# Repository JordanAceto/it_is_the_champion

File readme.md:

# 15 Watt Single Ended Tube Guitar Amp

- ## GU50 Pentode output
- ## Trainwreck style preamp
- ## It is the champion

---

## [SCHEMATIC](https://github.com/JordanAceto/it_is_the_champion/blob/main/pcb/docs/it_is_the_champion-schematic.pdf)

---
A prototype has been constructed and evaluated using a 6550 output tube. See the [prototype write up](https://github.com/JordanAceto/it_is_the_champion/blob/main/prototype/it_is_the_champion_prototype_write_up.pdf) for details. It sounds pretty good to me.

The GU50 output stage has been breadboarded. It seems to work well and gives a smidge more power out than the 6550 (I'm mostly just using it to be a hipster though).

Next steps:

Task | Status |
---------|--------------|
Schematic capture | &#9745;
PCB layout | &#9745;
Order boards and do test build | &#9745;
Front and rear panels | &#9745;
Generate complete BOM | &#9744;

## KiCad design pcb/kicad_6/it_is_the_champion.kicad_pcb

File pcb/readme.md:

# Kicad documents for the schematics and PCB layout

## The system consists of:
- ### Power supply PCB
- ### Preamp PCB
- ### Point to point wired power amp
- ### Chassis mount components (transformers, jacks, pots, etc)

The preamp and power supply pcbs are connected with breakaway mousebites.

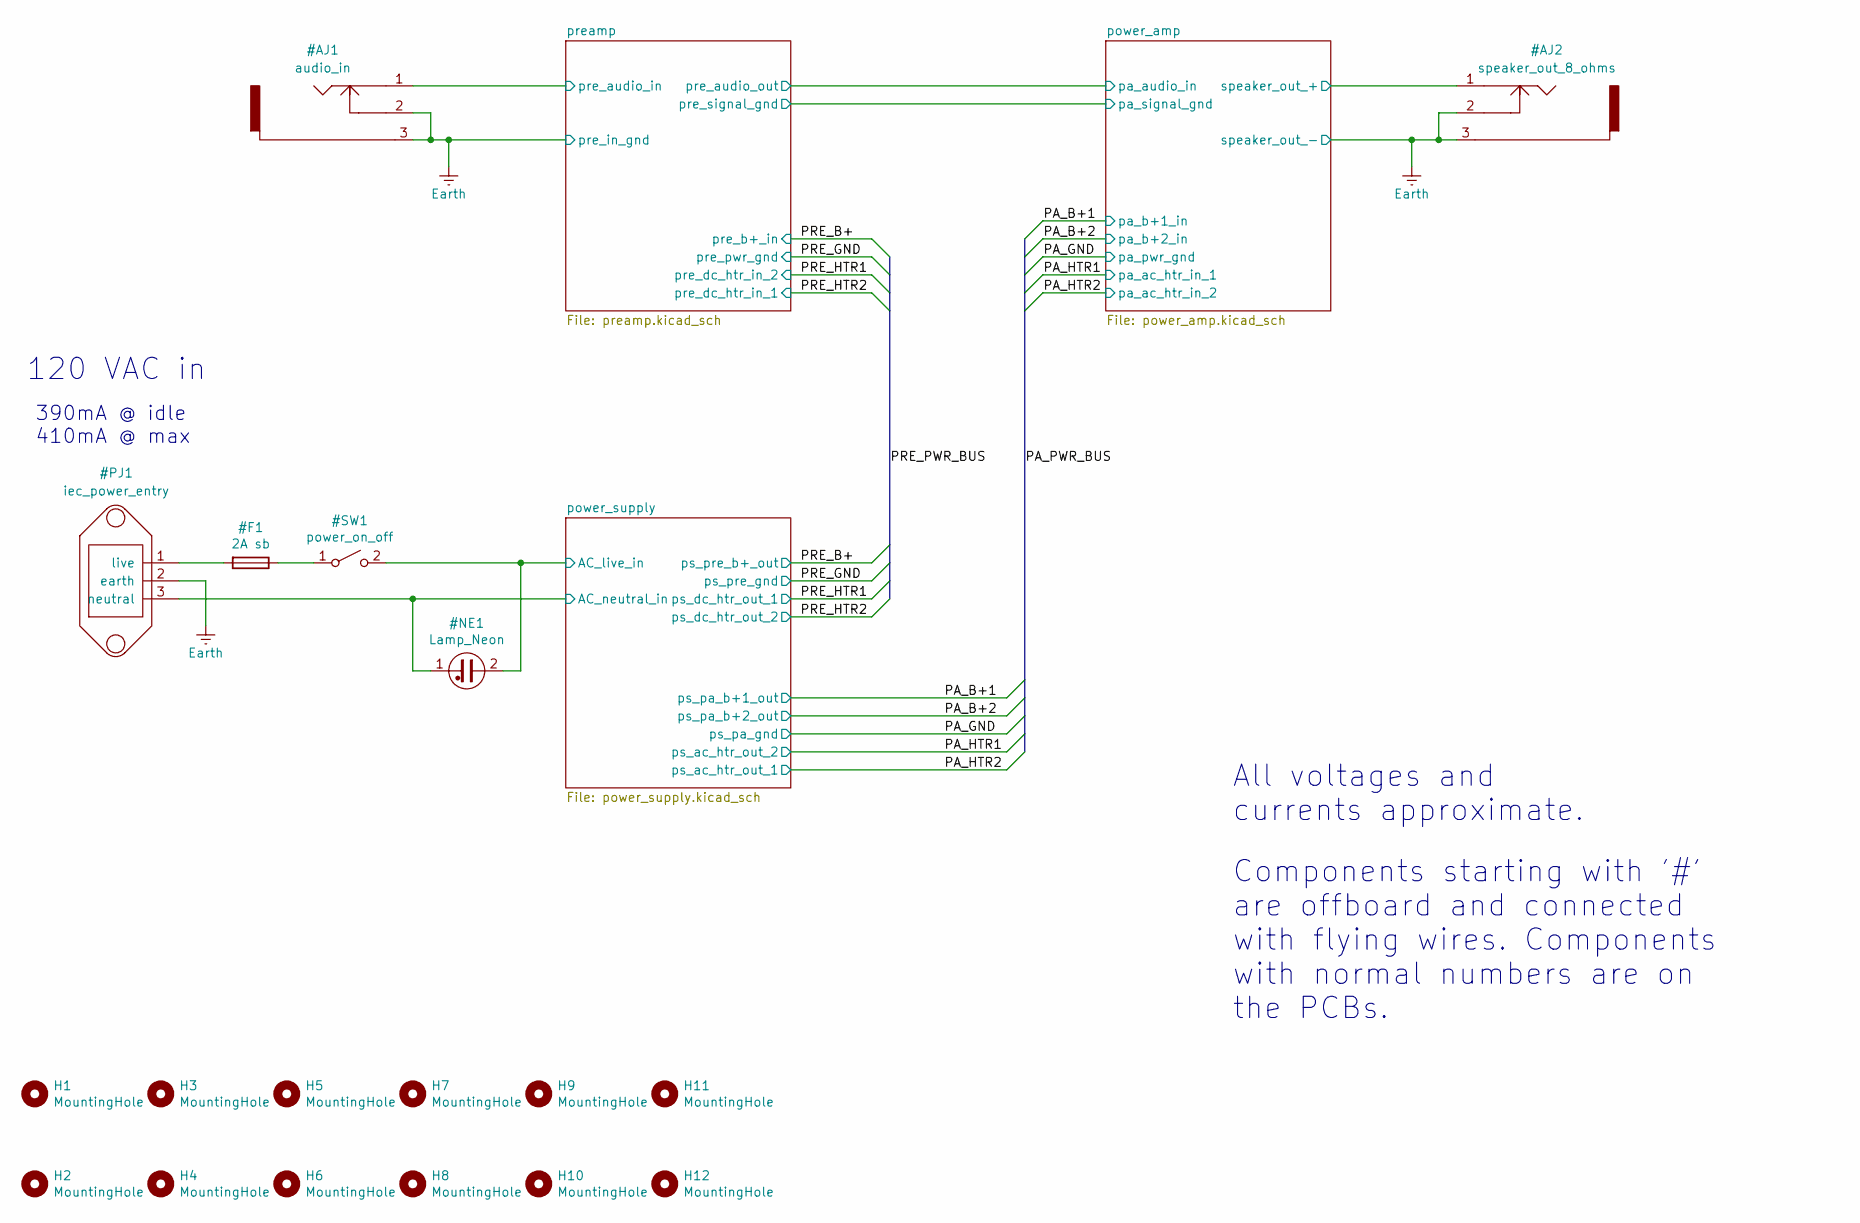
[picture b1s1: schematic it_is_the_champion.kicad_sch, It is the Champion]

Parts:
H1, H2, H3, H4, H5, H6, H7, H8, H9, H10, H11, H12: MountingHole; MountingHole_3.2mm_M3_DIN965_Pad

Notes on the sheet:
All voltages and currents approximate.
Components starting with '#' are offboard and connected with flying wires. Components with normal numbers are on the PCBs.
120 VAC in
390mA @ idle 410mA @ max

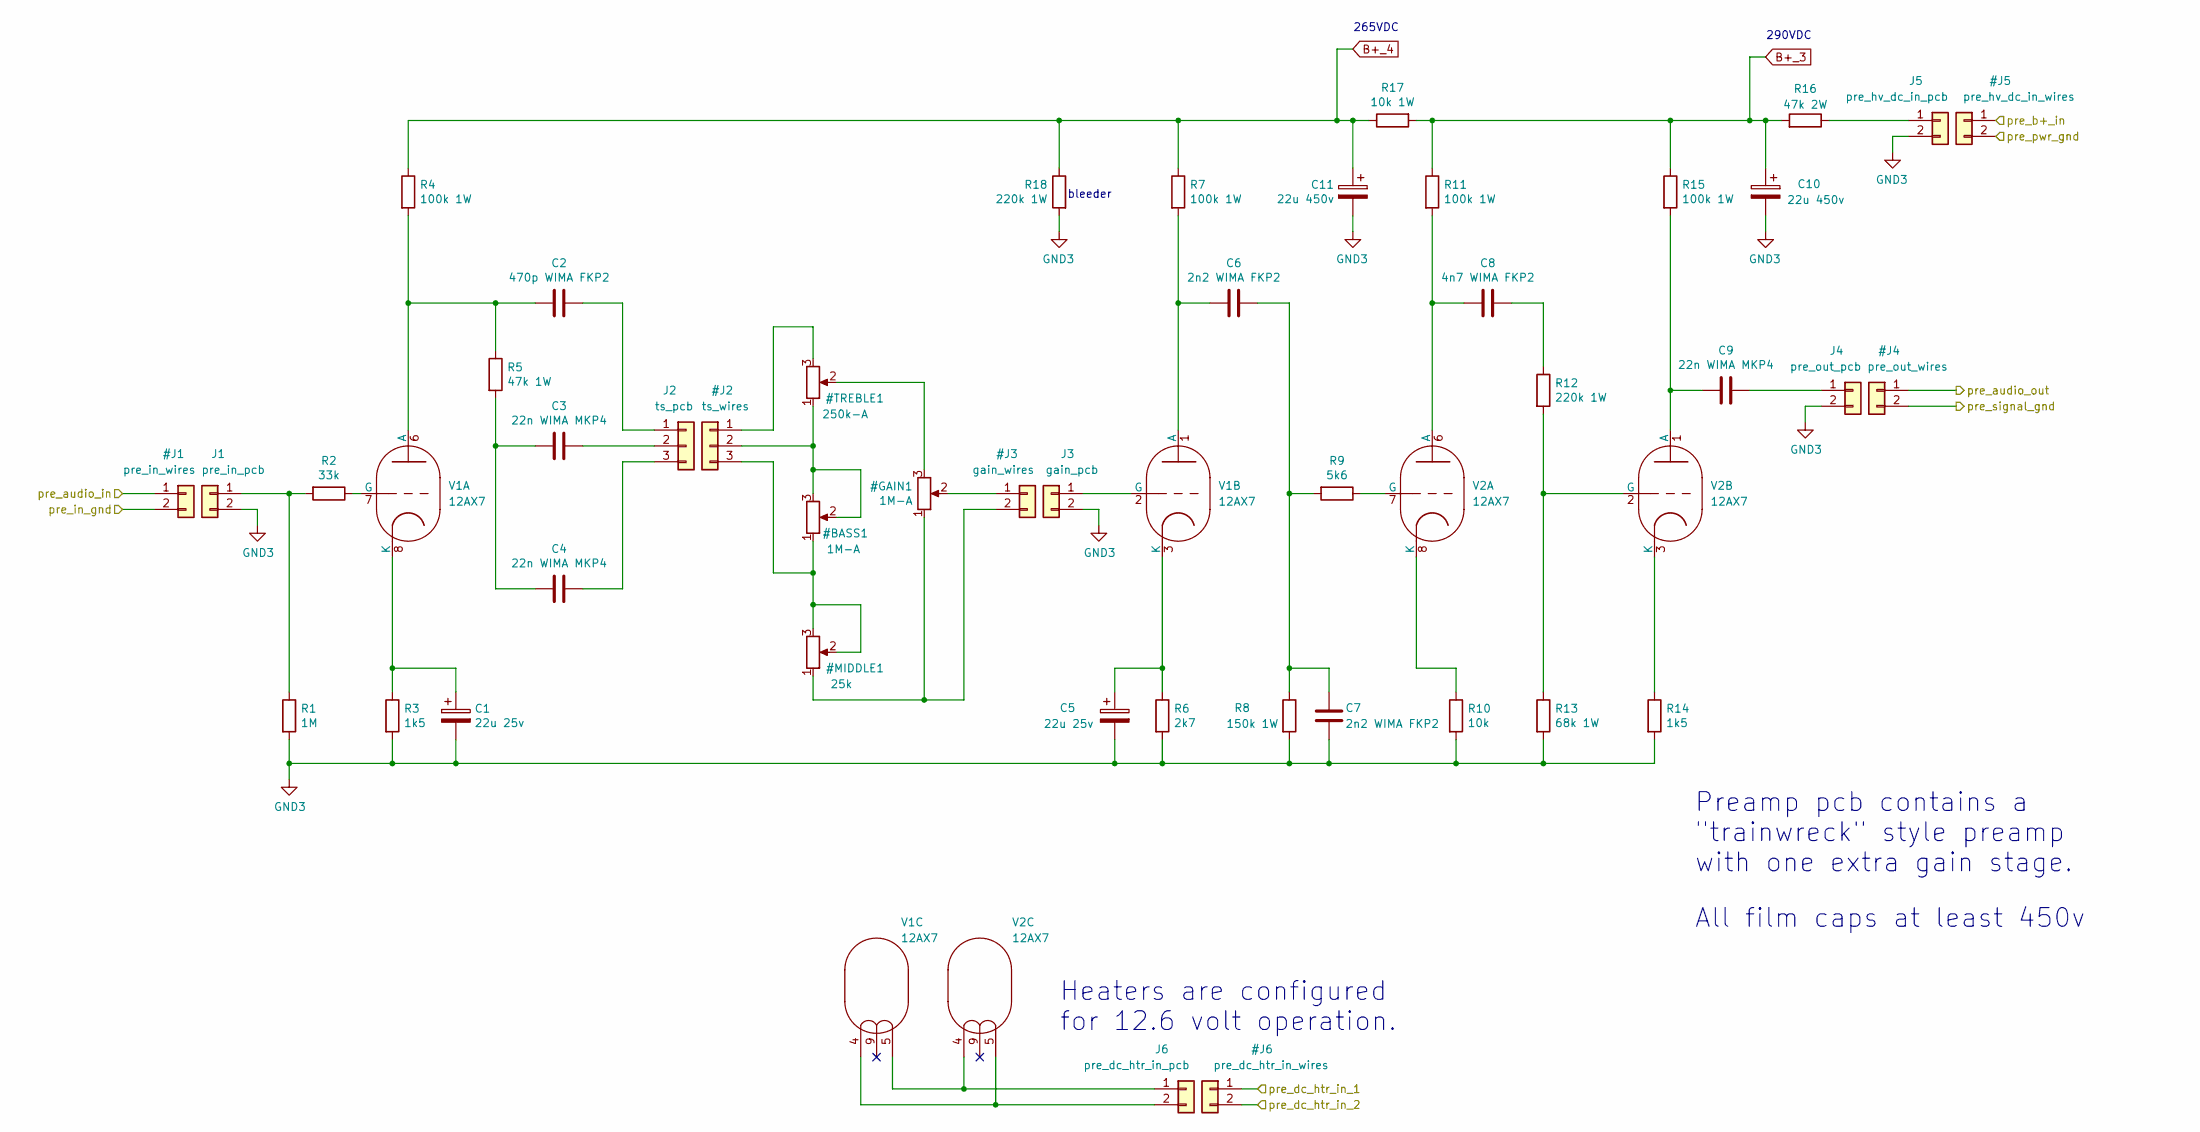
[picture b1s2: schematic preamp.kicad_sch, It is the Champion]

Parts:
C1, C5: 22u 25v; CP_Radial_D6.3mm_P2.50mm
C2: 470p WIMA FKP2; C_Rect_L7.2mm_W4.5mm_P5.00mm_FKS2_FKP2_MKS2_MKP2
C3, C4, C9: 22n WIMA MKP4; C_Rect_L13.0mm_W4.0mm_P10.00mm_FKS3_FKP3_MKS4
C6, C7: 2n2 WIMA FKP2; C_Rect_L7.2mm_W5.5mm_P5.00mm_FKS2_FKP2_MKS2_MKP2
C8: 4n7 WIMA FKP2; C_Rect_L7.2mm_W7.2mm_P5.00mm_FKS2_FKP2_MKS2_MKP2
C10, C11: 22u 450v; CP_Radial_D18.0mm_P7.50mm
J1: pre_in_pcb; signal_wire_connector_2
J2: ts_pcb; signal_wire_connector_3
J3: gain_pcb; signal_wire_connector_2
J4: pre_out_pcb; signal_wire_connector_2
J5: pre_hv_dc_in_pcb; SolderWire-0.75sqmm_1x02_P4.8mm_D1.25mm_OD2.3mm_Relief
J6: pre_dc_htr_in_pcb; SolderWire-0.75sqmm_1x02_P4.8mm_D1.25mm_OD2.3mm_Relief
R1: 1M; R_Axial_DIN0207_L6.3mm_D2.5mm_P10.16mm_Horizontal
R2: 33k; R_Axial_DIN0207_L6.3mm_D2.5mm_P10.16mm_Horizontal
R3, R14: 1k5; R_Axial_DIN0207_L6.3mm_D2.5mm_P10.16mm_Horizontal
R4, R7, R11, R15: 100k 1W; R_Axial_DIN0414_L11.9mm_D4.5mm_P20.32mm_Horizontal
R5: 47k 1W; R_Axial_DIN0414_L11.9mm_D4.5mm_P20.32mm_Horizontal
R6: 2k7; R_Axial_DIN0207_L6.3mm_D2.5mm_P10.16mm_Horizontal
R8: 150k 1W; R_Axial_DIN0414_L11.9mm_D4.5mm_P20.32mm_Horizontal
R9: 5k6; R_Axial_DIN0207_L6.3mm_D2.5mm_P10.16mm_Horizontal
R10: 10k; R_Axial_DIN0207_L6.3mm_D2.5mm_P10.16mm_Horizontal
R12, R18: 220k 1W; R_Axial_DIN0414_L11.9mm_D4.5mm_P20.32mm_Horizontal
R13: 68k 1W; R_Axial_DIN0414_L11.9mm_D4.5mm_P20.32mm_Horizontal
R16: 47k 2W; R_Axial_DIN0414_L11.9mm_D4.5mm_P20.32mm_Horizontal
R17: 10k 1W; R_Axial_DIN0414_L11.9mm_D4.5mm_P20.32mm_Horizontal
V1, V2: 12AX7; belton_VT9-PT-C

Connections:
B+_3: C10.1, R11.1, R15.1, R16.2, R17.2
B+_4: C11.1, R4.1, R7.1, R17.1, R18.1
GND3: C1.2, C5.2, C7.2, C10.2, C11.2, J1.2, J3.2, J4.2, J5.2, R1.2, R3.2, R6.2, R8.2, R10.2, R13.2, R14.2, R18.2
unnamed: C1.1, R3.1, V1.8 (K)
unnamed: C2.1, J2.1
unnamed: C2.2, R4.2, R5.1, V1.6 (A)
unnamed: C3.1, J2.2
unnamed: C3.2, C4.2, R5.2
unnamed: C4.1, J2.3
unnamed: C5.1, R6.1, V1.3 (K)
unnamed: C6.1, C7.1, R8.1, R9.2
unnamed: C6.2, R7.2, V1.1 (A)
unnamed: C8.1, R12.1
unnamed: C8.2, R11.2, V2.6 (A)
unnamed: C9.1, J4.1
unnamed: C9.2, R15.2, V2.1 (A)
unnamed: J1.1, R1.1, R2.2
unnamed: J3.1, V1.2 (G)
unnamed: J5.1, R16.1
unnamed: J6.1, V1.5, V2.4
unnamed: J6.2, V1.4, V2.5
unnamed: R2.1, V1.7 (G)
unnamed: R9.1, V2.7 (G)
unnamed: R10.1, V2.8 (K)
unnamed: R12.2, R13.1, V2.2 (G)
unnamed: R14.1, V2.3 (K)

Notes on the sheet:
Preamp pcb contains a "trainwreck" style preamp with one extra gain stage.
bleeder
Heaters are configured for 12.6 volt operation.
290VDC
265VDC
All film caps at least 450v

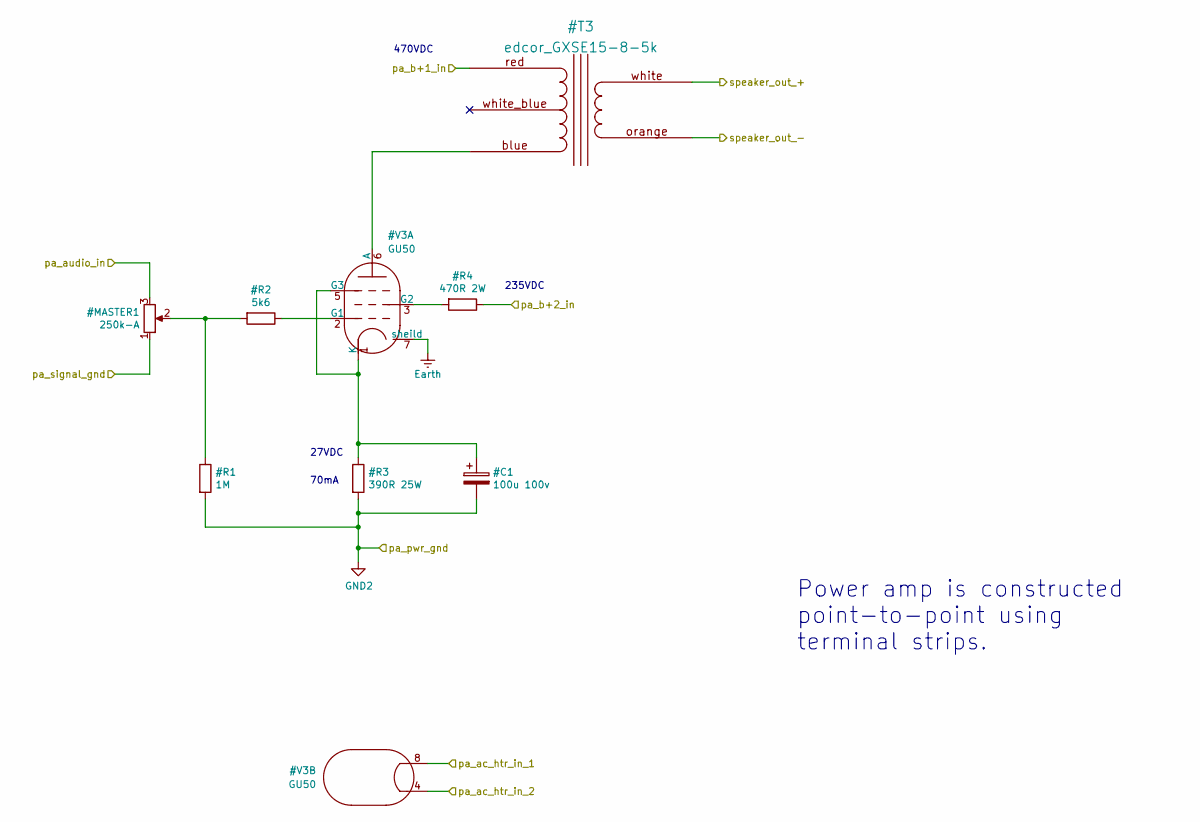
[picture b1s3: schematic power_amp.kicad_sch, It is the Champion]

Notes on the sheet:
470VDC
235VDC
70mA
27VDC
Power amp is constructed point-to-point using terminal strips.

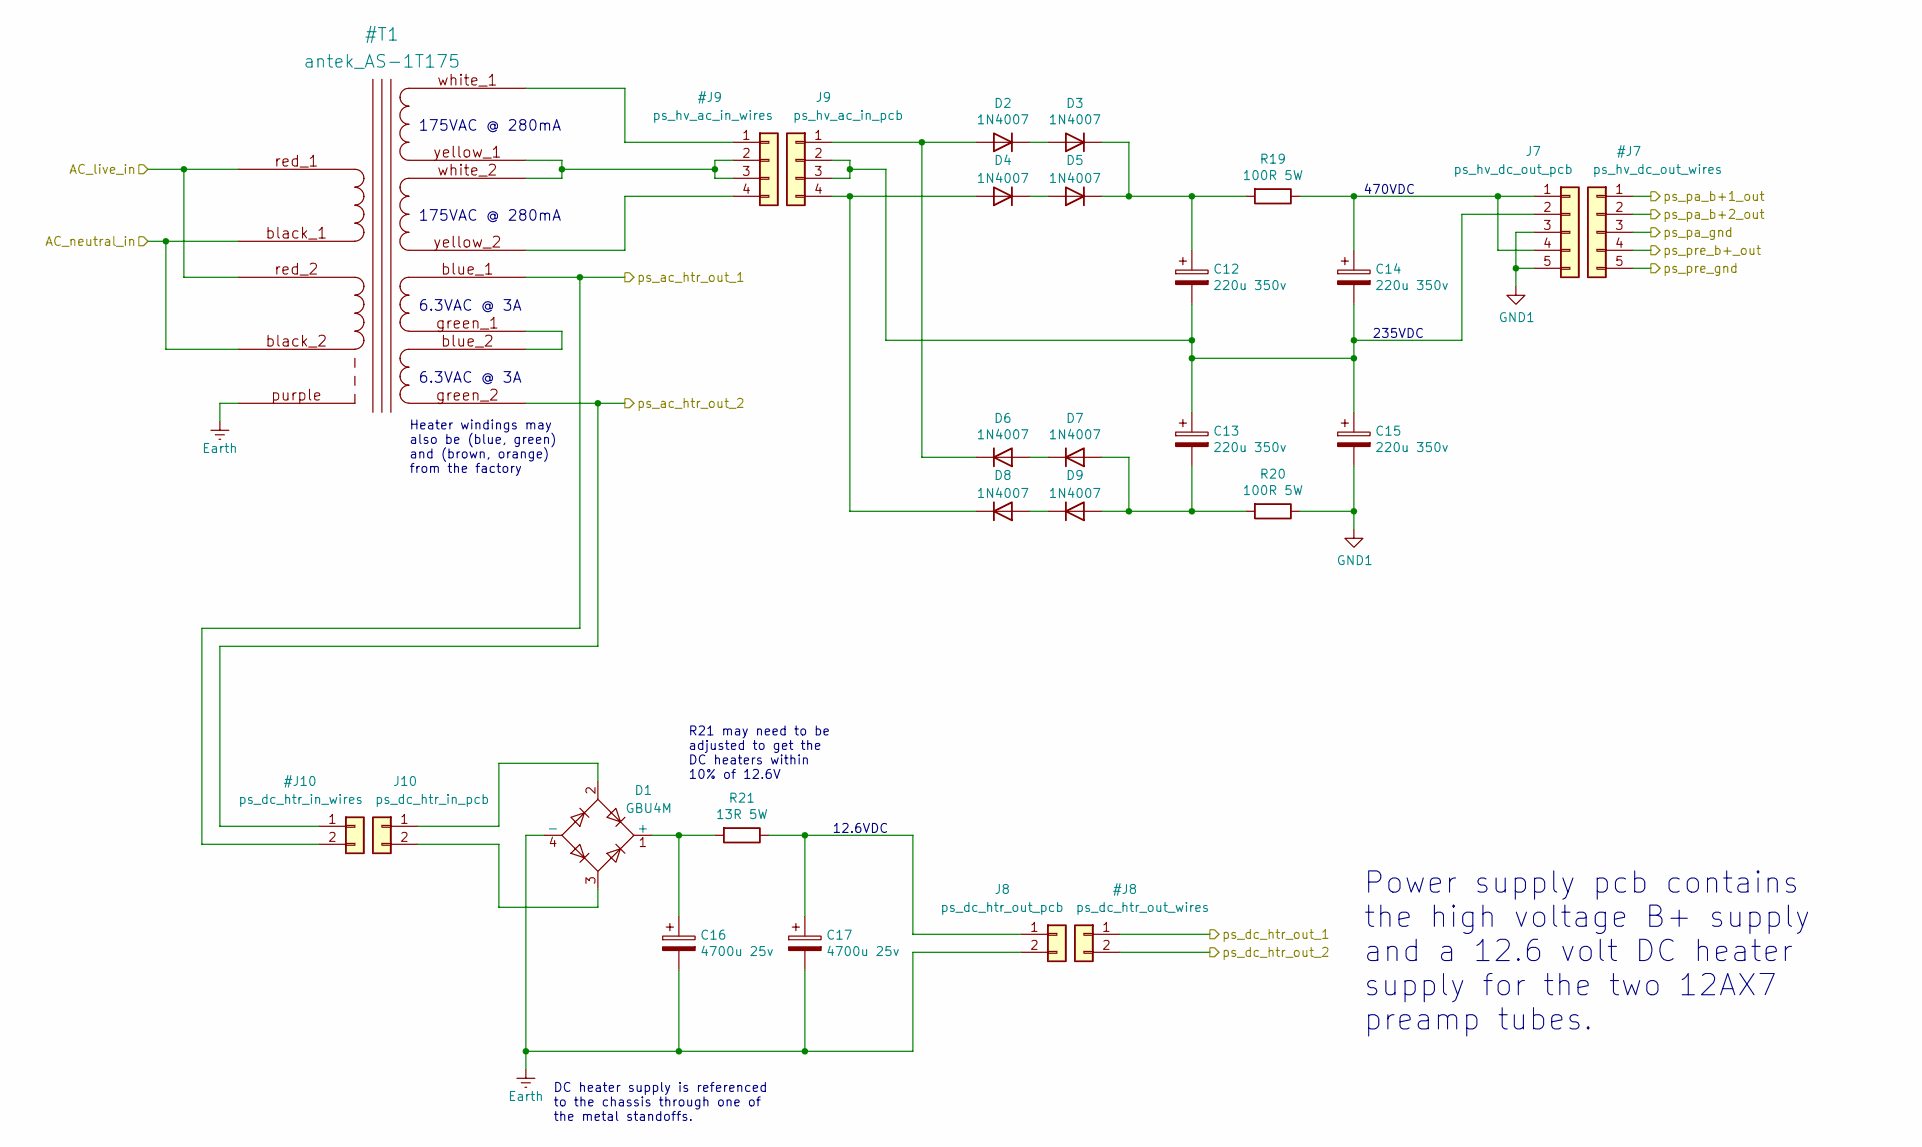
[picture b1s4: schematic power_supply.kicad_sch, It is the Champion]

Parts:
C12, C13, C14, C15: 220u 350v; CP_Radial_D18.0mm_P7.50mm
C16, C17: 4700u 25v; CP_Radial_D16.0mm_P7.50mm
D1: GBU4M; Diode_Bridge_Vishay_GBU
D2, D3, D4, D5, D6, D7, D8, D9: 1N4007; D_DO-41_SOD81_P10.16mm_Horizontal
J7: ps_hv_dc_out_pcb; SolderWire-0.75sqmm_1x05_P4.8mm_D1.25mm_OD2.3mm_Relief
J8: ps_dc_htr_out_pcb; SolderWire-0.75sqmm_1x02_P4.8mm_D1.25mm_OD2.3mm_Relief
J9: ps_hv_ac_in_pcb; SolderWire-0.75sqmm_1x04_P4.8mm_D1.25mm_OD2.3mm_Relief
J10: ps_dc_htr_in_pcb; SolderWire-0.75sqmm_1x02_P4.8mm_D1.25mm_OD2.3mm_Relief
R19, R20: 100R 5W; R_Axial_DIN0617_L17.0mm_D6.0mm_P30.48mm_Horizontal
R21: 13R 5W; R_Axial_DIN0617_L17.0mm_D6.0mm_P30.48mm_Horizontal

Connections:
Earth: C16.2, C17.2, D1.4 (-), J8.2
GND1: C15.2, J7.3, J7.5, R20.1
unnamed: C12.1, D3.1 (K), D5.1 (K), R19.2
unnamed: C12.2, C13.1, C14.2, C15.1, J7.2, J9.2, J9.3
unnamed: C13.2, D7.2 (A), D9.2 (A), R20.2
unnamed: C14.1, J7.1, J7.4, R19.1
unnamed: C16.1, D1.1 (+), R21.2
unnamed: C17.1, J8.1, R21.1
unnamed: D1.2, J10.1
unnamed: D1.3, J10.2
unnamed: D2.1 (K), D3.2 (A)
unnamed: D2.2 (A), D6.1 (K), J9.1
unnamed: D4.1 (K), D5.2 (A)
unnamed: D4.2 (A), D8.1 (K), J9.4
unnamed: D6.2 (A), D7.1 (K)
unnamed: D8.2 (A), D9.1 (K)

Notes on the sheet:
175VAC @ 280mA
470VDC
12.6VDC
DC heater supply is referenced to the chassis through one of the metal standoffs.
6.3VAC @ 3A
R21 may need to be adjusted to get the DC heaters within 10% of 12.6V
Power supply pcb contains the high voltage B+ supply and a 12.6 volt DC heater supply for the two 12AX7 preamp tubes.
Heater windings may also be (blue, green) and (brown, orange) from the factory
235VDC

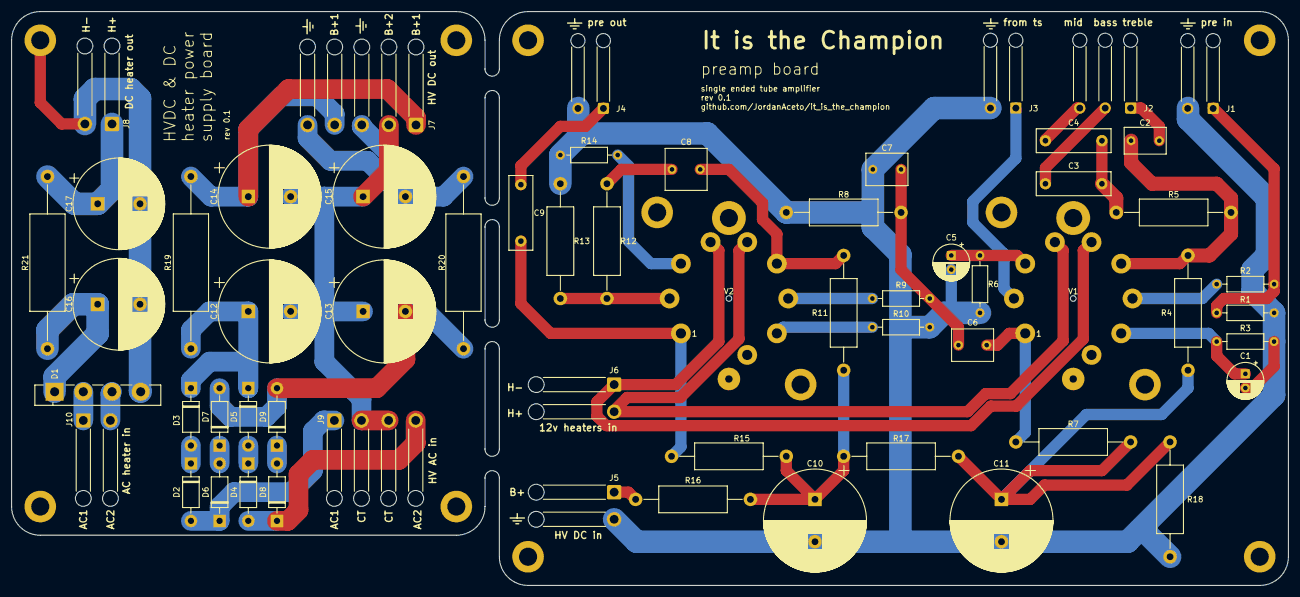
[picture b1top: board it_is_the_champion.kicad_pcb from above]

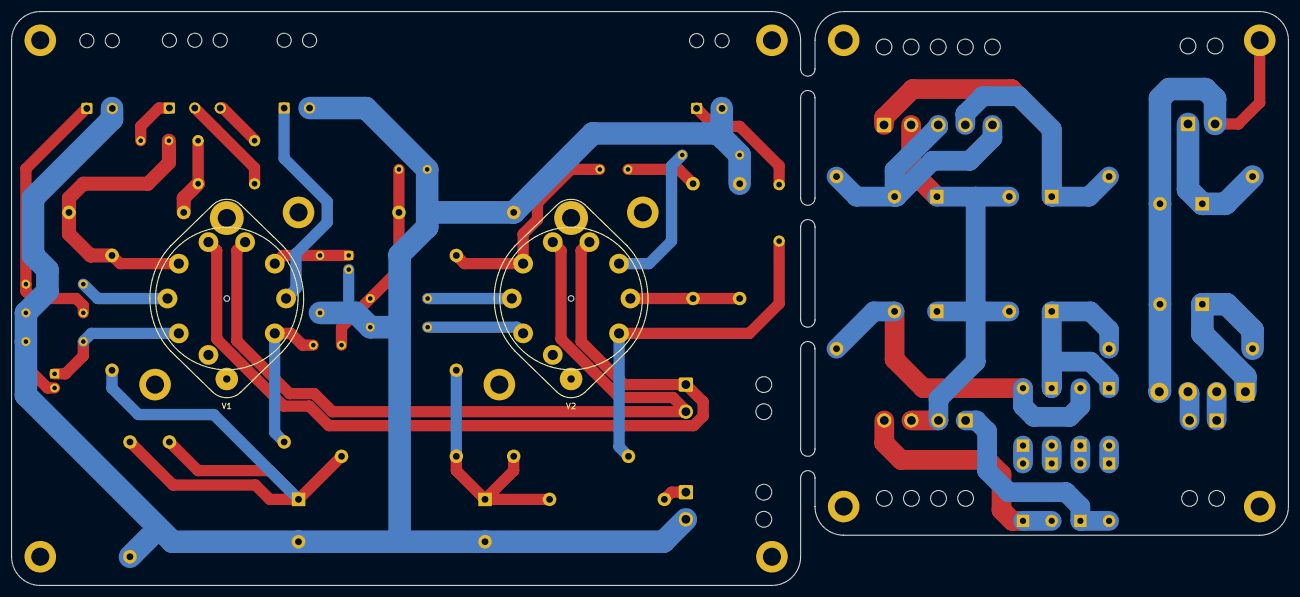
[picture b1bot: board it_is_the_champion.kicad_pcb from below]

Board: 2 copper layers, 226.1 x 101.6 mm, 71 parts (2 on the bottom side), 42 nets.

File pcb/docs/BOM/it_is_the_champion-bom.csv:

Row,Description,Part,References,Value,Footprint,Quantity Per PCB,Status,Datasheet
1,Unpolarized capacitor,C,C2,470p WIMA FKP2,C_Rect_L7.2mm_W4.5mm_P5.00mm_FKS2_FKP2_MKS2_MKP2,1, ,~
2,Unpolarized capacitor,C,C6 C7,2n2 WIMA FKP2,C_Rect_L7.2mm_W5.5mm_P5.00mm_FKS2_FKP2_MKS2_MKP2,2, ,~
3,Unpolarized capacitor,C,C8,4n7 WIMA FKP2,C_Rect_L7.2mm_W7.2mm_P5.00mm_FKS2_FKP2_MKS2_MKP2,1, ,~
4,Unpolarized capacitor,C,C3 C4 C9,22n WIMA MKP4,C_Rect_L13.0mm_W4.0mm_P10.00mm_FKS3_FKP3_MKS4,3, ,~
5,Polarized capacitor,C_Polarized,C1 C5,22u 25v,CP_Radial_D6.3mm_P2.50mm,2, ,~
6,Polarized capacitor,C_Polarized,C10 C11,22u 450v,CP_Radial_D18.0mm_P7.50mm,2, ,~
7,Polarized capacitor,C_Polarized,C12 C13 C14 C15,220u 350v,CP_Radial_D18.0mm_P7.50mm,4, ,~
8,Polarized capacitor,C_Polarized,C16 C17,4700u 25v,CP_Radial_D16.0mm_P7.50mm,2, ,~
9,"1000V 1A General Purpose Rectifier Diode, DO-41",1N4007,D2 D3 D4 D5 D6 D7 D8 D9,1N4007,D_DO-41_SOD81_P10.16mm_Horizontal,8, ,http://www.vishay.com/docs/88503/1n4001.pdf
10,"Single-Phase Bridge Rectifier, 700V Vrms, 4.0A If, GBU package",GBU4M,D1,GBU4M,Diode_Bridge_Vishay_GBU,1, ,http://www.vishay.com/docs/88656/gbu4a.pdf
11,Resistor,R,R21,13R 5W,R_Axial_DIN0617_L17.0mm_D6.0mm_P30.48mm_Horizontal,1, ,~
12,Resistor,R,R19 R20,100R 5W,R_Axial_DIN0617_L17.0mm_D6.0mm_P30.48mm_Horizontal,2, ,~
13,Resistor,R,R3 R14,1k5,R_Axial_DIN0207_L6.3mm_D2.5mm_P10.16mm_Horizontal,2, ,~
14,Resistor,R,R6,2k7,R_Axial_DIN0207_L6.3mm_D2.5mm_P10.16mm_Horizontal,1, ,~
15,Resistor,R,R9,5k6,R_Axial_DIN0207_L6.3mm_D2.5mm_P10.16mm_Horizontal,1, ,~
16,Resistor,R,R10,10k,R_Axial_DIN0207_L6.3mm_D2.5mm_P10.16mm_Horizontal,1, ,~
17,Resistor,R,R17,10k 1W,R_Axial_DIN0414_L11.9mm_D4.5mm_P20.32mm_Horizontal,1, ,~
18,Resistor,R,R2,33k,R_Axial_DIN0207_L6.3mm_D2.5mm_P10.16mm_Horizontal,1, ,~
19,Resistor,R,R5 R16,47k 1W,R_Axial_DIN0414_L11.9mm_D4.5mm_P20.32mm_Horizontal,2, ,~
20,Resistor,R,R13,68k 1W,R_Axial_DIN0414_L11.9mm_D4.5mm_P20.32mm_Horizontal,1, ,~
21,Resistor,R,R4 R7 R11 R15,100k 1W,R_Axial_DIN0414_L11.9mm_D4.5mm_P20.32mm_Horizontal,4, ,~
22,Resistor,R,R8,150k 1W,R_Axial_DIN0414_L11.9mm_D4.5mm_P20.32mm_Horizontal,1, ,~
23,Resistor,R,R12 R18,220k 1W,R_Axial_DIN0414_L11.9mm_D4.5mm_P20.32mm_Horizontal,2, ,~
24,Resistor,R,R1,1M,R_Axial_DIN0207_L6.3mm_D2.5mm_P10.16mm_Horizontal,1, ,~
25,,12AX7,V1 V2,12AX7,belton_VT9-PT-C,2, ,





Project info:
Schematic:,it_is_the_champion
Variant:,default
Revision:,0.1
Date:,2022-07-16
KiCad Version:,6.0.6-3a73a75311~116~ubuntu22.04.1
Statistics:
Component Groups:,25
Component Count:,49 (0 SMD/ 47 THT)
Fitted Components:,49 (0 SMD/ 47 THT)
Number of PCBs:,1
Total Components:,49

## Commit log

2021-08-18 move schematic to top level
2021-08-18 tweak DC heater, pcb, regenerate build files
2021-08-19 start write-up for prototype evaluation
2021-08-19 reduce gain in last preamp stage
2021-08-25 tweak prototype, add to proto write-up
2021-12-13 change PA to GU50, respin pcb
2021-12-21 add screen wire to power xformer
2021-12-30 make rear panel
2021-12-30 rear panel organization, gerbers
2021-12-30 update gitignore for kicad 6
2021-12-30 update pcb for kicad 6
2021-12-30 moce schematic, update readme
2021-12-31 fix capacitor name typo
2021-12-31 update faceplate dir for kicad 6, add warnings
2022-01-04 tweak some values
2022-01-05 check box after test build
2022-07-16 Update faceplate and rear panel
2022-07-16 Improve pcb documentation
2022-07-16 Tweaks to KiCad pcb project

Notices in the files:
pcb/kicad_6/it_is_the_champion.kicad_pcb:
creativecommons.org/licenses/by/4.0
License: CC by 4.0
